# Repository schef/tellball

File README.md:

# tellball
Maturalni rad u KiCad-u

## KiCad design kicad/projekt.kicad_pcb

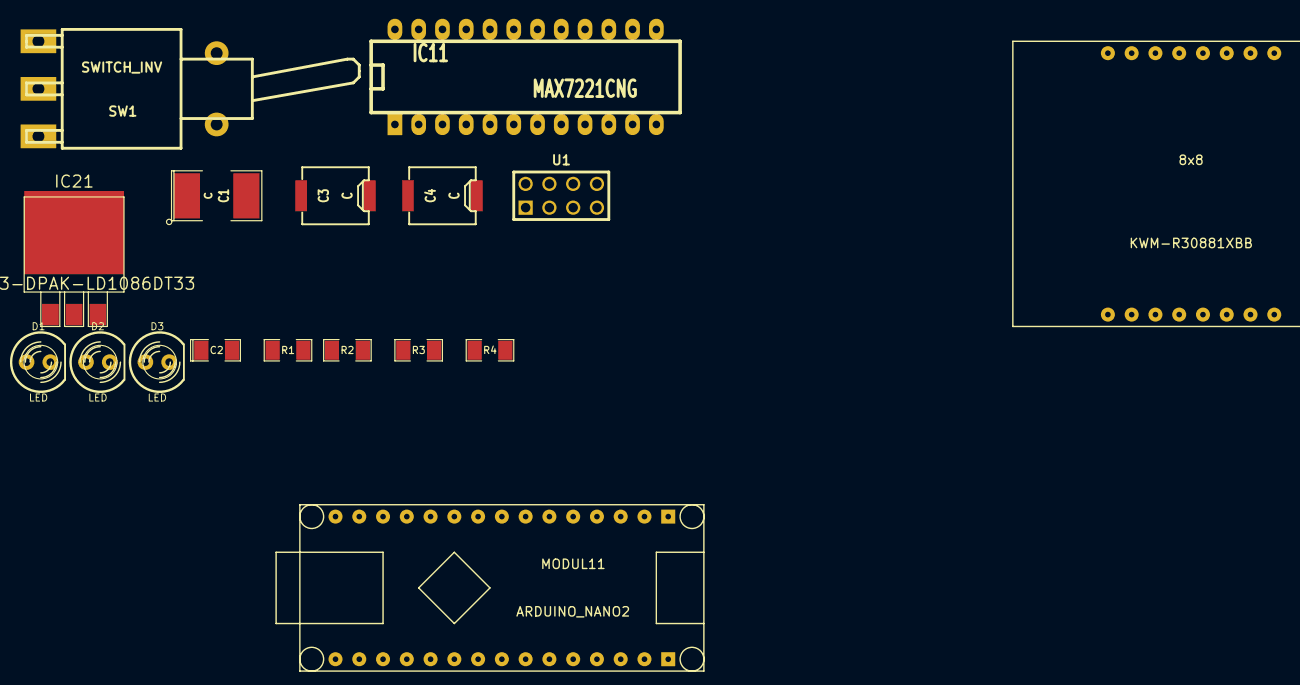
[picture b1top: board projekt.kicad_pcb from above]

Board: 2 copper layers, 17 parts (0 on the bottom side), 23 nets, no tracks yet.

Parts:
8x8: KWM-R30881XBB
C1: C; SM2112L
C2: CAPAPOL; SM1206POL
C3, C4: C; SMD403
D1, D2, D3: LED; LED-5MM
IC11: MAX7221CNG; DIP-24__400_ELL
IC21: CREG3-DPAK-LD1086DT33; DPAK3
MODUL11: ARDUINO_NANO2
R1, R2, R3, R4: R; SM1206
SW1: SWITCH_INV; SW_SPDT
U1: SV; pin_array_4x2

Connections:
+5V: C1.1, C2.1, C3.1, IC11.19, IC21.1, R1.1, SW1.1
+BATT: C1.2, C2.2, C3.2, C4.2, D1.2, D2.2, D3.2, IC11.4, IC11.9, SW1.2, U1.1
unnamed: 8x8.14, IC11.11
unnamed: 8x8.9, IC11.2
unnamed: 8x8.11, IC11.21
unnamed: 8x8.5, IC11.8
unnamed: 8x8.4, IC11.16
unnamed: 8x8.3, IC11.14
unnamed: 8x8.2, IC11.5
unnamed: 8x8.1, IC11.3
unnamed: 8x8.15, IC11.15
unnamed: 8x8.13, IC11.22
unnamed: 8x8.6, IC11.23
unnamed: 8x8.10, IC11.20
unnamed: 8x8.16, IC11.17
unnamed: 8x8.8, IC11.6
unnamed: 8x8.7, IC11.10
unnamed: 8x8.12, IC11.7
unnamed: IC11.18, R1.2
unnamed: D3.1, R2.2
unnamed: D2.1, R3.2
unnamed: D1.1, R4.2
VCC: C4.1, IC21.3, U1.2

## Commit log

2015-05-23 up we go
